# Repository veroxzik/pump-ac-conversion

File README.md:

# Pump AC Conversion

This repo contains files for my hyper-specific desire to get rid of all the rusted metal and busted sensors from my Pump It Up arcade pads.

It features the odd choice to keep bracketed panels, due to cost. In the future, I may modify the files to also support bracketless panels.

## Code

The code is designed around RP2040. Install the [arduino-pico](https://github.com/earlephilhower/arduino-pico) core and compiled using the [Arduino IDE](https://www.arduino.cc/en/software). 

At the top of the code lists `panelPins`, an array grouping 4 pins for each of the 5 panels. You can change these if you are not using the boards as I've designed.
```c
int panelPins[5][4] =
  {
    {0, 1, 2, 3},
    {4, 5, 6, 7},
    {8, 9, 10, 11},
    {12, 13, 14, 15},
    {16, 17, 18, 19}
  };
```

This code is simplistic. There's no debounce. If any switch is triggered, it will trigger the entire panel.

## CAD

New frames were designed to be 3D printed (as all of mine were rusted). They are designed to use the existing bracketed panels and replaces the sensors with [cheap generic dance sensors](https://rhythm-cons.wiki/controllers/dance-pads/dance-pads/#sensors). 

The frames are modular, consisting of corner supports and a choice of two side segments to form either the square or rectangle frames. A small printed top goes on the sensor to distribute the load and provide a place to tape mod.

A partial assembly is shown below:

## Boards

Two boards are contained in this repo.

### Pad Board

The pad board takes a Raspberry Pi Pico as the main microcontroller, and has several JST XH connectors to mate with the connector boards, discussed below. There's also another JST XH connector for a WS2812B output, and for USB input.

### Connector Boards

The connector boards are designed to screw into the area where the L-Bracket is mounted. Two are required for each panel. Each daughter board has (2) JST XH 2P connectors for the generic dance sensor, (2) JST XH 3P connectors for linking two connector boards together (OUT on one board goes to IN on the other), and (2) JST XH 5P connectors to bring signals back to the pad board (only one is necessary to use, but both are included for easier wire routing.

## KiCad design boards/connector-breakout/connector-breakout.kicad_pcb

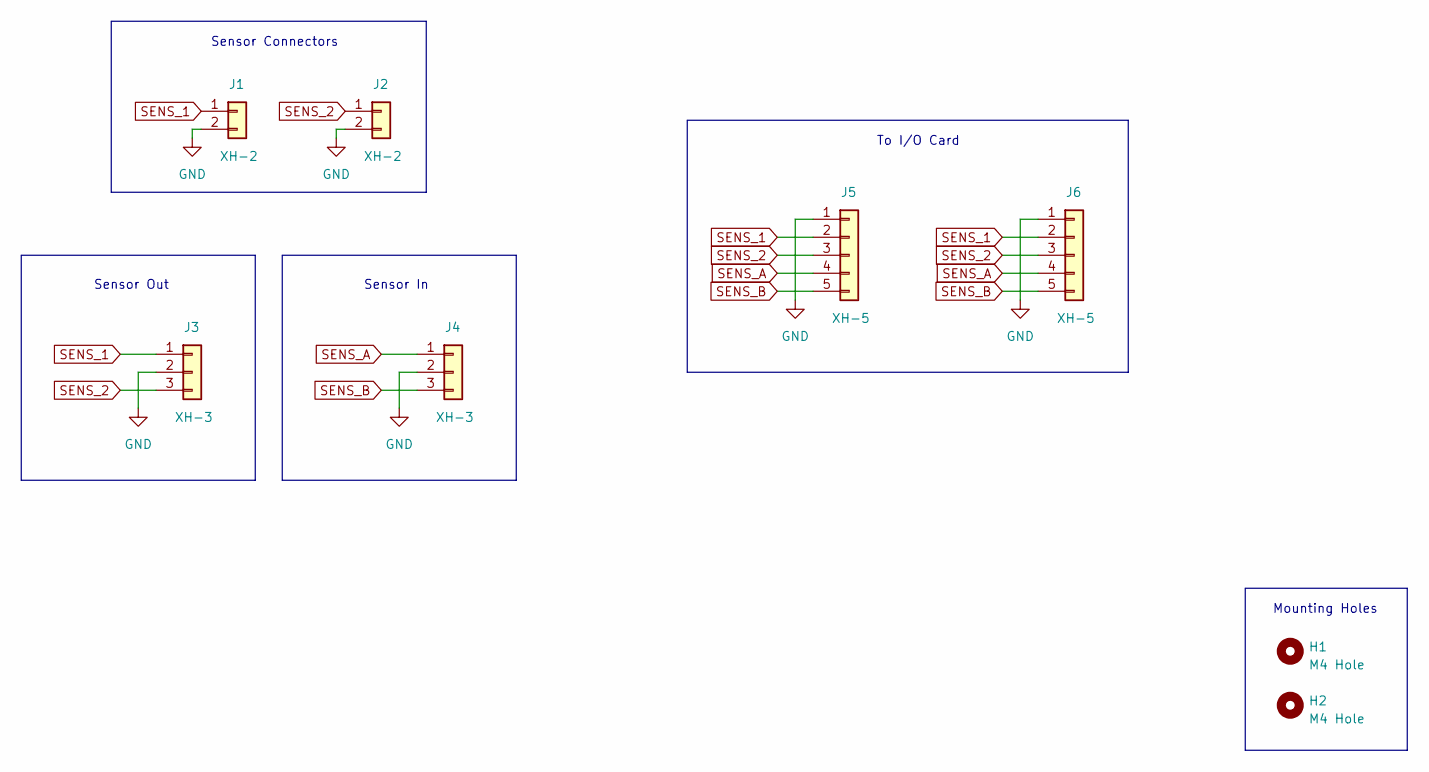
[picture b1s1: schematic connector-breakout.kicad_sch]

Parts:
H1, H2: M4 Hole; MountingHole_4.3mm_M4
J1, J2: XH-2; JST_XH_B2B-XH-A_1x02_P2.50mm_Vertical
J3, J4: XH-3; JST_XH_S3B-XH-A-1_1x03_P2.50mm_Horizontal
J5, J6: XH-5; JST_XH_S5B-XH-A-1_1x05_P2.50mm_Horizontal

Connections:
GND: J1.2, J2.2, J3.2, J4.2, J5.1, J6.1
SENS_1: J1.1, J3.1, J5.2, J6.2
SENS_2: J2.1, J3.3, J5.3, J6.3
SENS_A: J4.1, J5.4, J6.4
SENS_B: J4.3, J5.5, J6.5

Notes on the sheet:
Sensor Connectors
Sensor In
Mounting Holes
To I/O Card
Sensor Out

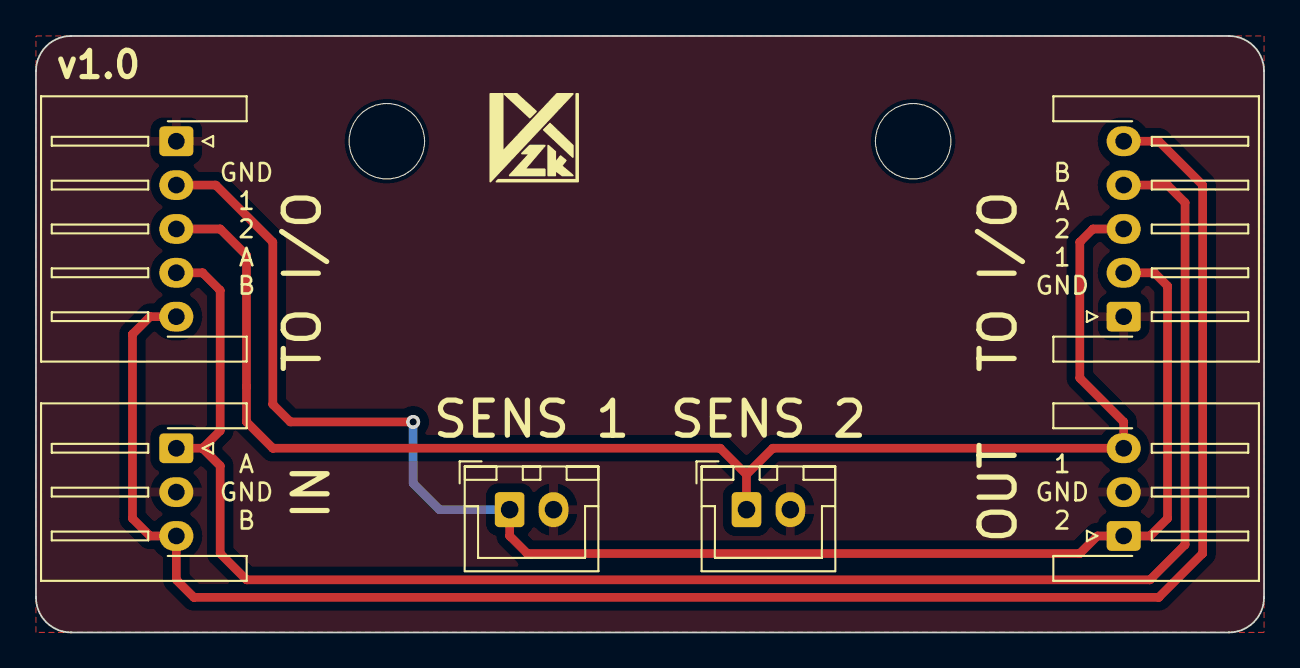
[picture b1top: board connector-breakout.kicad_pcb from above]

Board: 2 copper layers, 70.0 x 34.0 mm, 8 parts (0 on the bottom side), 5 nets.

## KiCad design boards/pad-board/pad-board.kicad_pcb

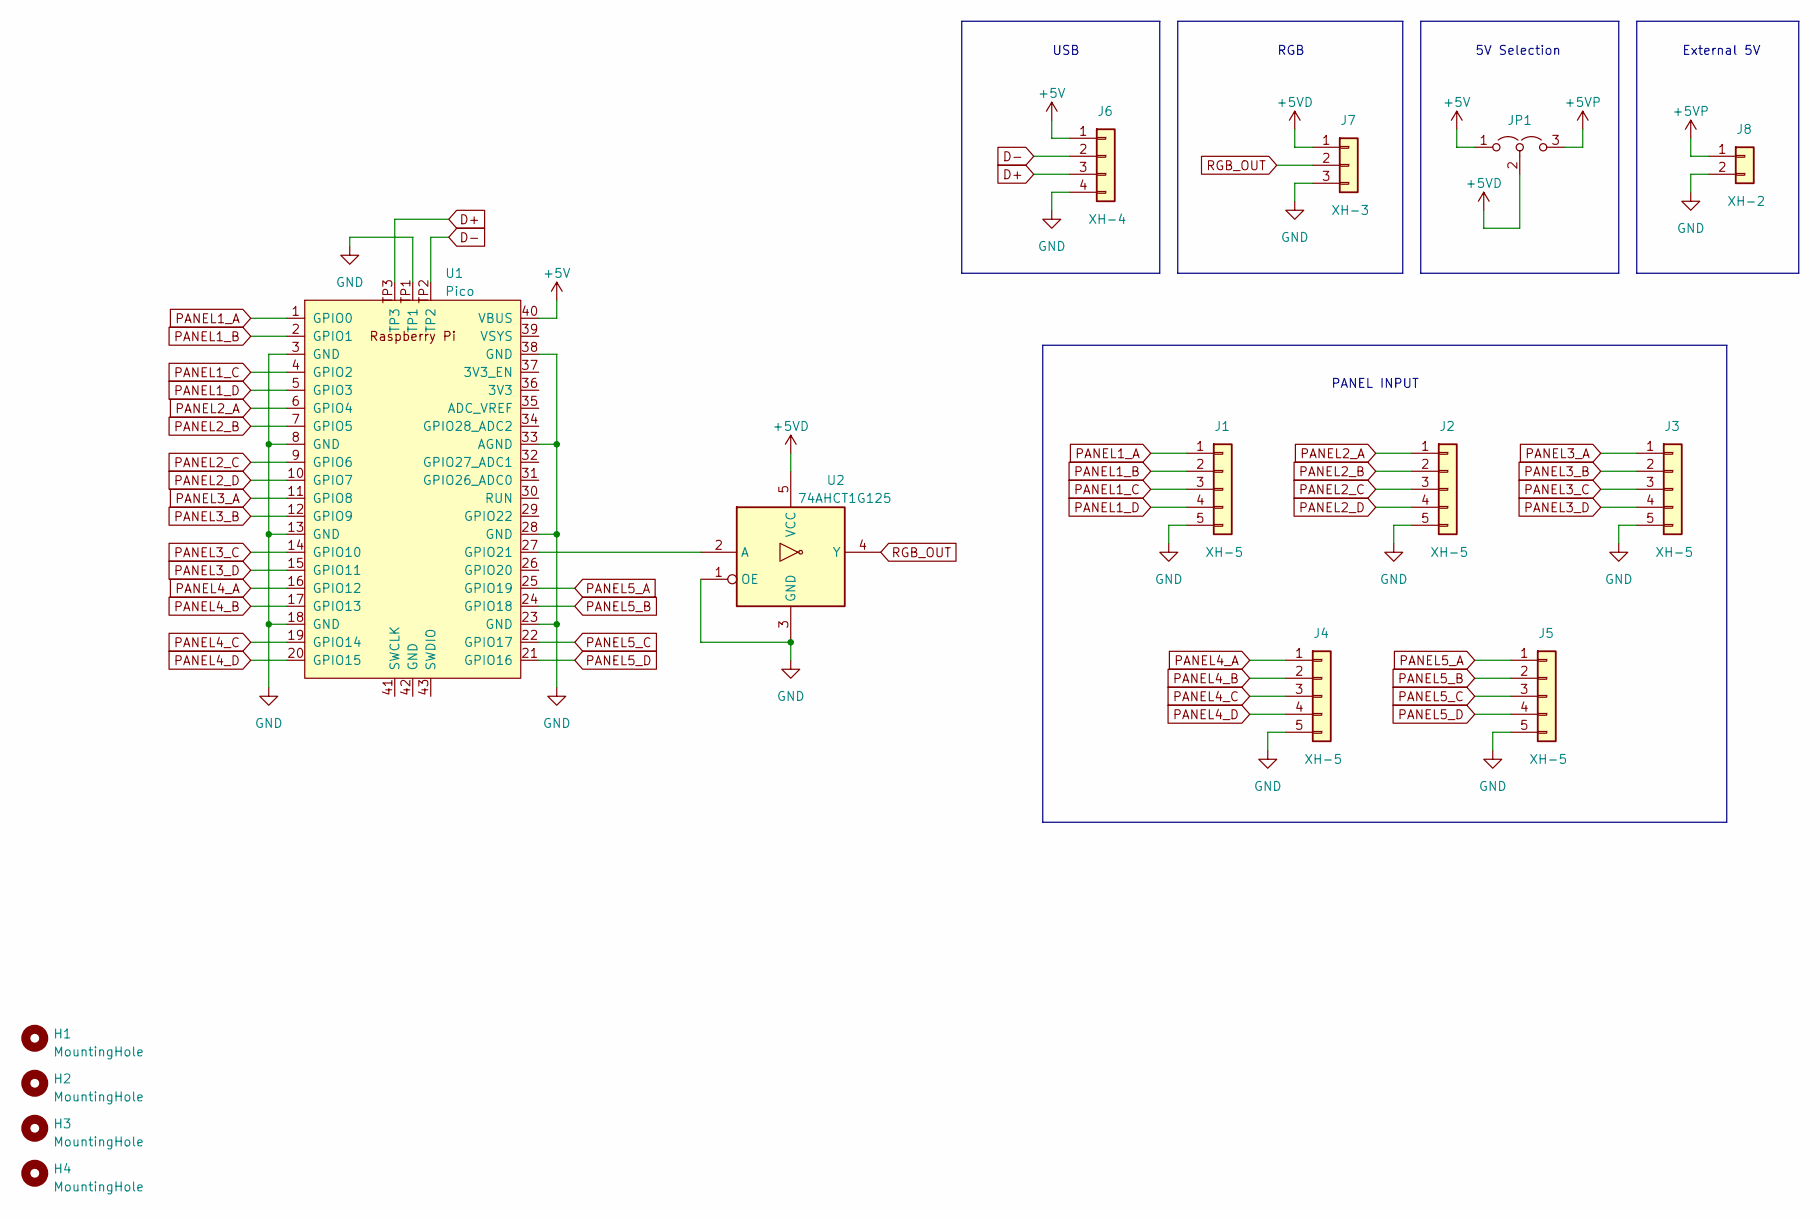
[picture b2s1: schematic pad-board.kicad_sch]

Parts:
H1, H2, H3, H4: MountingHole; MountingHole_3.2mm_M3_DIN965_Pad
J1, J2, J3, J4, J5: XH-5; JST_XH_S5B-XH-A-1_1x05_P2.50mm_Horizontal
J6: XH-4; JST_XH_S4B-XH-A-1_1x04_P2.50mm_Horizontal
J7: XH-3; JST_XH_S3B-XH-A-1_1x03_P2.50mm_Horizontal
J8: XH-2; JST_XH_S2B-XH-A-1_1x02_P2.50mm_Horizontal
JP1: Jumper_3_Open; SolderJumper-3_P2.0mm_Open_TrianglePad1.0x1.5mm
U1: Pico; RPi_Pico_SMD_TH
U2: 74AHCT1G125; SOT-23-5_HandSoldering

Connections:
+5V: J6.1, JP1.1 (A), U1.40 (VBUS)
+5VD: J7.1, JP1.2 (C), U2.5 (VCC)
+5VP: J8.1, JP1.3 (B)
D+: J6.3, U1.TP3
D-: J6.2, U1.TP2
GND: J1.5, J2.5, J3.5, J4.5, J5.5, J6.4, J7.3, J8.2, U1.3 (GND), U1.8 (GND), U1.13 (GND), U1.18 (GND), U1.23 (GND), U1.28 (GND), U1.33 (AGND), U1.38 (GND), U1.TP1, U2.1 (OE), U2.3 (GND)
unnamed: U1.27 (GPIO21), U2.2 (A)
PANEL1_A: J1.1, U1.1 (GPIO0)
PANEL1_B: J1.2, U1.2 (GPIO1)
PANEL1_C: J1.3, U1.4 (GPIO2)
PANEL1_D: J1.4, U1.5 (GPIO3)
PANEL2_A: J2.1, U1.6 (GPIO4)
PANEL2_B: J2.2, U1.7 (GPIO5)
PANEL2_C: J2.3, U1.9 (GPIO6)
PANEL2_D: J2.4, U1.10 (GPIO7)
PANEL3_A: J3.1, U1.11 (GPIO8)
PANEL3_B: J3.2, U1.12 (GPIO9)
PANEL3_C: J3.3, U1.14 (GPIO10)
PANEL3_D: J3.4, U1.15 (GPIO11)
PANEL4_A: J4.1, U1.16 (GPIO12)
PANEL4_B: J4.2, U1.17 (GPIO13)
PANEL4_C: J4.3, U1.19 (GPIO14)
PANEL4_D: J4.4, U1.20 (GPIO15)
PANEL5_A: J5.1, U1.25 (GPIO19)
PANEL5_B: J5.2, U1.24 (GPIO18)
PANEL5_C: J5.3, U1.22 (GPIO17)
PANEL5_D: J5.4, U1.21 (GPIO16)
RGB_OUT: J7.2, U2.4 (Y)

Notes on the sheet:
External 5V
PANEL INPUT
5V Selection
RGB
USB

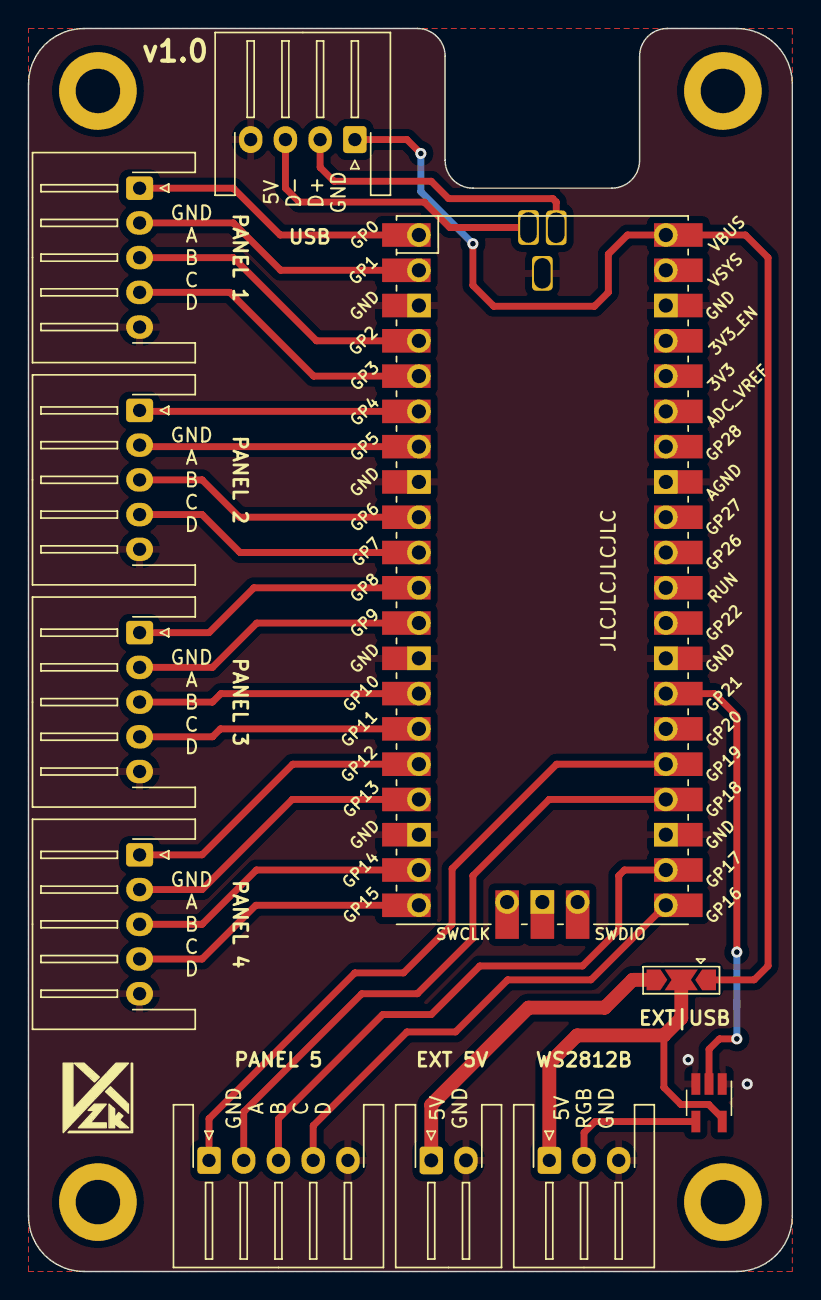
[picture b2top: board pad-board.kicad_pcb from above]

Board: 2 copper layers, 55.0 x 89.5 mm, 15 parts (0 on the bottom side), 28 nets.

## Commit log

2024-04-26 Initial commit.
2024-04-26 Upload code
2024-07-18 Adding CAD for frames.
2024-11-05 Add README and CAD for the connecting plate.
